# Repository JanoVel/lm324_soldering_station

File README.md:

# lm324_soldering_station
Here are the KiCad files of my (analog soldering station)[http://electronics.vlzqz.com/analog-closed-loop-controlled-soldering-station.html]

There are both SVGs with the PCB layout, as well as KiCad files so that the desing can be adapted.

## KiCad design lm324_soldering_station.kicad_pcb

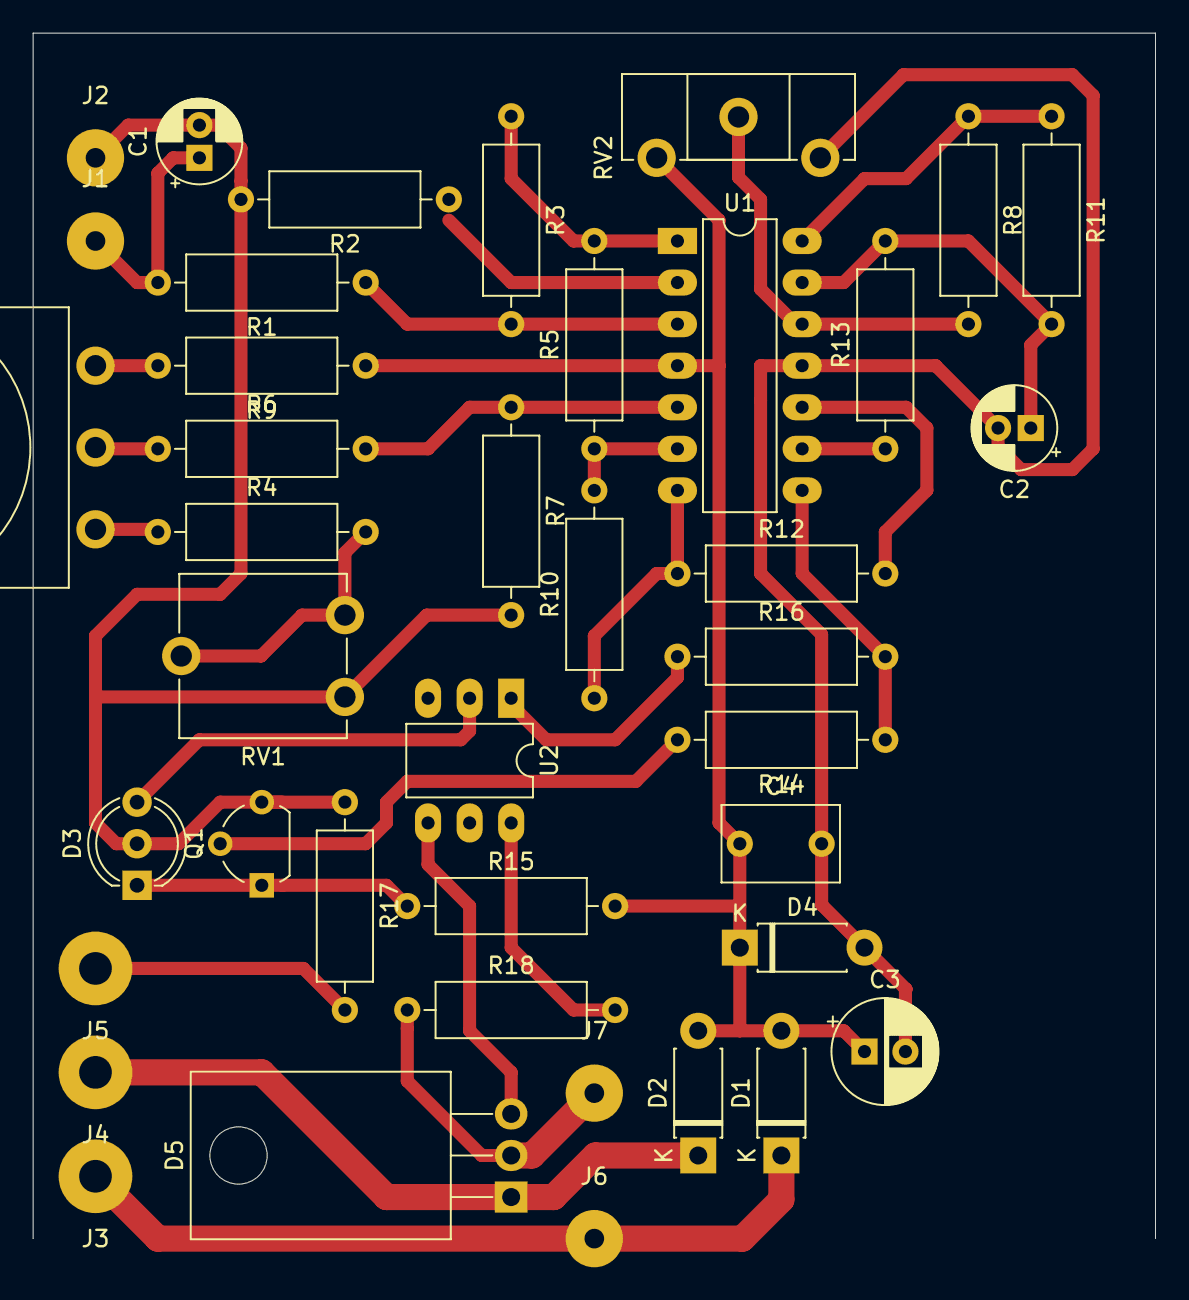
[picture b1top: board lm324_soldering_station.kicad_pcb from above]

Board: 2 copper layers, 68.6 x 73.7 mm, 40 parts (0 on the bottom side), 29 nets.

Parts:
C1: 10nF; CP_Radial_D5.0mm_P2.00mm
C2: 1uF; CP_Radial_D5.0mm_P2.00mm
C3: 100uF; CP_Radial_D6.3mm_P2.50mm
C4: 100nF; C_Rect_L7.0mm_W4.5mm_P5.00mm
D1, D2: 1N4007; D_DO-41_SOD81_P7.62mm_Horizontal
D3: LED_Dual_ACA; LED_D5.0mm-3
D4: 1N4742; D_DO-41_SOD81_P7.62mm_Horizontal
D5: BTA08; TO-220-3_Horizontal_TabDown
J1: TC +; SolderWirePad_1x01_Drill1.2mm
J2: TC -; SolderWirePad_1x01_Drill1.2mm
J3: 24VAC L; SolderWirePad_1x01_Drill2mm
J4: 24VAC N; SolderWirePad_1x01_Drill2mm
J5: 24AC G; SolderWirePad_1x01_Drill2mm
J6: HEATER A; SolderWirePad_1x01_Drill1.2mm
J7: HEATER B; SolderWirePad_1x01_Drill1.2mm
Q1: BC337; TO-92L_Wide
R1, R5, R6, R12, R13, R14: 10k; R_Axial_DIN0309_L9.0mm_D3.2mm_P12.70mm_Horizontal
R2, R3, R16: 1k; R_Axial_DIN0309_L9.0mm_D3.2mm_P12.70mm_Horizontal
R4: 4.7k; R_Axial_DIN0309_L9.0mm_D3.2mm_P12.70mm_Horizontal
R7, R10: 1M; R_Axial_DIN0309_L9.0mm_D3.2mm_P12.70mm_Horizontal
R8: 1.2k; R_Axial_DIN0309_L9.0mm_D3.2mm_P12.70mm_Horizontal
R9: 56k; R_Axial_DIN0309_L9.0mm_D3.2mm_P12.70mm_Horizontal
R11: 22k; R_Axial_DIN0309_L9.0mm_D3.2mm_P12.70mm_Horizontal
R15: 1.5k; R_Axial_DIN0309_L9.0mm_D3.2mm_P12.70mm_Horizontal
R17: 220; R_Axial_DIN0309_L9.0mm_D3.2mm_P12.70mm_Horizontal
R18: 39; R_Axial_DIN0309_L9.0mm_D3.2mm_P12.70mm_Horizontal
RV1: 1k; Potentiometer_ACP_CA9-V10_Vertical
RV2: 50k; Potentiometer_ACP_CA14-H2,5_Horizontal
RV3: 5k; Potentiometer_Omeg_PC16BU_Vertical
U1: LM324; DIP-14_W7.62mm_LongPads
U2: MOC3041M; DIP-6_W7.62mm_LongPads

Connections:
/AC_GND: J5.1, R17.2
/AC_L: D1.1, J3.1, J6.1
/AC_N: D2.1, D5.1, J4.1
GND: C1.2, C2.2, C3.2, C4.2, D3.2, D4.2, J2.1, Q1.3, R2.2, R7.2, R17.1, RV1.3, RV2.3, U1.11
unnamed: C1.1, J1.1, R1.2
unnamed: C2.1, R11.2, R13.2, U1.13
unnamed: D3.1, Q1.1, R15.1
unnamed: D3.3, U2.2
unnamed: D5.2, J7.1, R18.1
unnamed: D5.3, U2.4
unnamed: Q1.2, R14.2
unnamed: R1.1, R3.2, U1.3
unnamed: R2.1, U1.2
unnamed: R3.1, R5.2, U1.1
unnamed: R4.1, RV3.3
unnamed: R4.2, RV1.1, RV1.2
unnamed: R6.1, RV3.2
unnamed: R6.2, R7.1, U1.5
unnamed: R8.2, RV2.2, U1.12
unnamed: R9.2, RV3.1
unnamed: R10.1, R12.1, U1.7
unnamed: R5.1, R10.2, U1.6
unnamed: R8.1, R11.1, U1.14
unnamed: R12.2, U1.10
unnamed: R13.1, U1.9
unnamed: R14.1, R16.2, U1.8
unnamed: R16.1, U2.1
unnamed: R18.2, U2.6
VCC: C3.1, C4.1, D1.2, D2.2, D4.1, R9.1, R15.2, RV2.1, U1.4

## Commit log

2020-03-11 Added project files
    Added the KiCad project files
2020-03-11 Added fab layer SVG
